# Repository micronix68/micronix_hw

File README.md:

# micronix_hw
Micronix Motorola 68000 Microcomputer hardware development repository

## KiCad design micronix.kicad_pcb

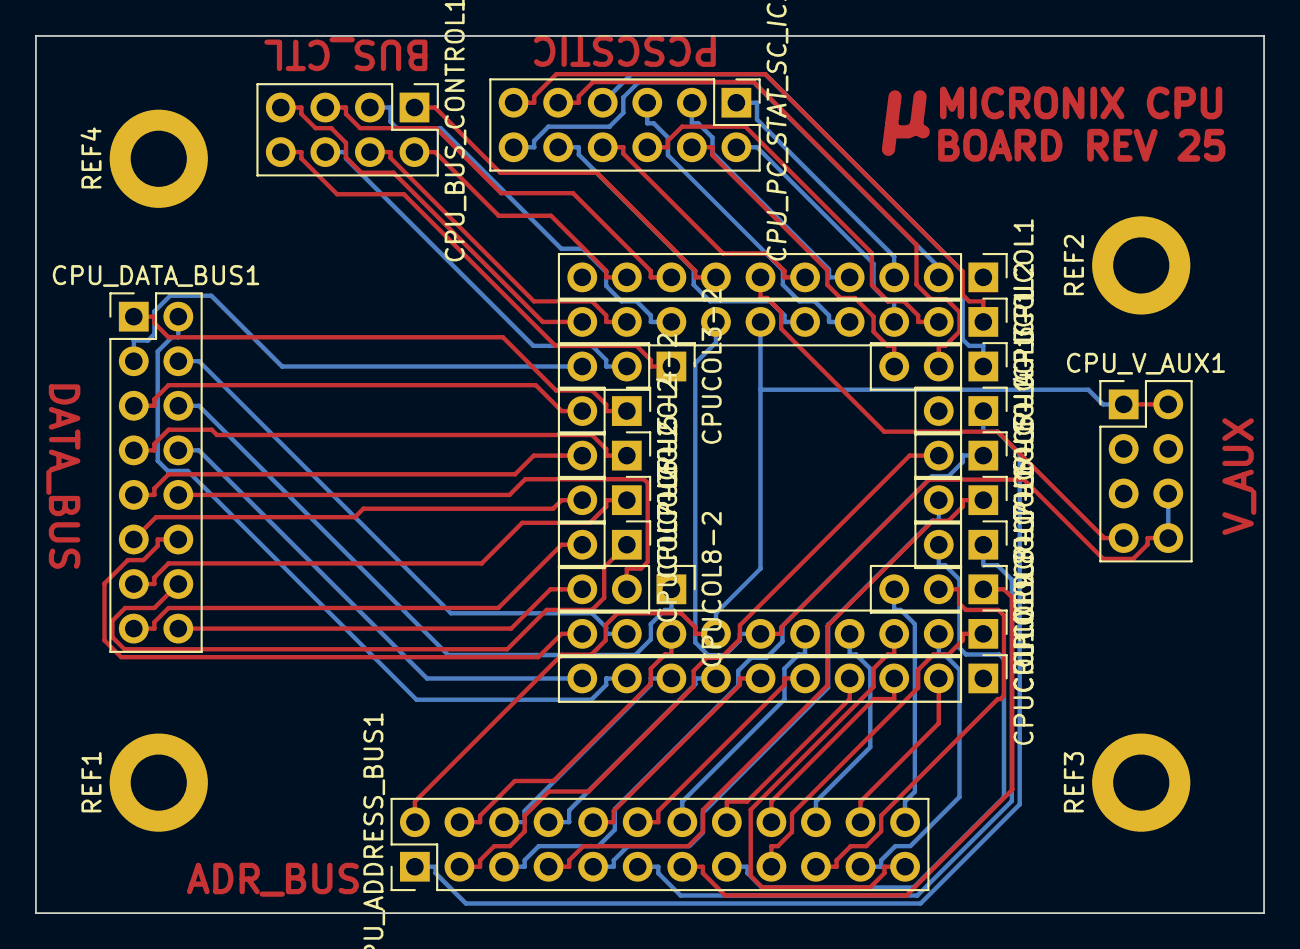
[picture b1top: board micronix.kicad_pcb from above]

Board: 2 copper layers, 70.0 x 50.0 mm, 25 parts (0 on the bottom side), 62 nets.

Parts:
CPUCOL1, CPUCOL2, CPUCOL9, CPUCOL10: Conn_01x10_Female; PinHeader_1x10_P2.54mm_Vertical
CPUCOL3-1, CPUCOL3-2, CPUCOL8-1, CPUCOL8-2: Conn_01x03_Female; PinHeader_1x03_P2.54mm_Vertical
CPUCOL4-1, CPUCOL4-2, CPUCOL5-1, CPUCOL5-2, CPUCOL6-1, CPUCOL6-2, CPUCOL7-1, CPUCOL7-2: Conn_01x02_Female; PinHeader_1x02_P2.54mm_Vertical
CPU_ADDRESS_BUS1: Conn_02x12_Odd_Even; PinHeader_2x12_P2.54mm_Vertical
CPU_BUS_CONTROL1: Conn_02x04_Odd_Even; PinHeader_2x04_P2.54mm_Vertical
CPU_DATA_BUS1: Conn_02x08_Odd_Even; PinHeader_2x08_P2.54mm_Vertical
CPU_PC_STAT_SC_IC1: Conn_02x06_Odd_Even; PinHeader_2x06_P2.54mm_Vertical
CPU_V_AUX1: Conn_02x04_Odd_Even; PinHeader_2x04_P2.54mm_Vertical
REF1, REF2, REF3, REF4: MountingHole_3.2mm_M3_DIN965_Pad

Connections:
/A2: CPUCOL2.10, CPU_BUS_CONTROL1.7
/A3: CPUCOL3-2.3, CPU_DATA_BUS1.3
/A4: CPUCOL4-2.2, CPU_DATA_BUS1.5
/A5: CPUCOL5-2.2, CPU_DATA_BUS1.9
/A6: CPUCOL6-2.2, CPU_DATA_BUS1.11
/A7: CPUCOL7-2.2, CPU_DATA_BUS1.15
/A8: CPUCOL8-2.3, CPU_DATA_BUS1.16
/A9: CPUCOL9.10, CPU_DATA_BUS1.12
/A10: CPUCOL10.10, CPU_DATA_BUS1.8
/B1: CPUCOL1.9, CPU_BUS_CONTROL1.2
/B2: CPUCOL2.9, CPU_BUS_CONTROL1.4
/B3: CPUCOL3-2.2, CPU_BUS_CONTROL1.6
/B4: CPUCOL4-2.1, CPU_DATA_BUS1.1
/B5: CPUCOL5-2.1, CPU_DATA_BUS1.7
/B6: CPUCOL6-2.1, CPU_DATA_BUS1.13
/B7: CPUCOL7-2.1, CPU_DATA_BUS1.14
/B8: CPUCOL8-2.2, CPU_DATA_BUS1.10
/B9: CPUCOL9.9, CPU_DATA_BUS1.4
/B10: CPUCOL10.9, CPU_DATA_BUS1.2
/C1: CPUCOL1.8, CPU_BUS_CONTROL1.5
/C2: CPUCOL2.8, CPU_BUS_CONTROL1.3
/C3: CPUCOL3-2.1, CPU_BUS_CONTROL1.8
/C8: CPUCOL8-2.1, CPU_DATA_BUS1.6
/C9: CPUCOL9.8, CPU_ADDRESS_BUS1.4
/C10: CPUCOL10.8, CPU_ADDRESS_BUS1.6
/D1: CPUCOL1.7, CPU_BUS_CONTROL1.1
/D2: CPUCOL2.7, CPUCOL9.6, CPU_V_AUX1.6, CPU_V_AUX1.8
/D9: CPUCOL2.6, CPUCOL9.7, CPU_ADDRESS_BUS1.2, CPU_V_AUX1.1, CPU_V_AUX1.2
/D10: CPUCOL10.7, CPU_ADDRESS_BUS1.8
/E1: CPUCOL1.6, CPU_V_AUX1.7
/E10: CPUCOL10.6, CPU_ADDRESS_BUS1.10
/F1: CPUCOL1.5, CPU_PC_STAT_SC_IC1.8
/F2: CPUCOL2.5, CPU_PC_STAT_SC_IC1.10
/F9: CPUCOL9.5, CPU_ADDRESS_BUS1.14
/F10: CPUCOL10.5, CPU_ADDRESS_BUS1.12
/G1: CPUCOL1.4, CPU_PC_STAT_SC_IC1.3
/G2: CPUCOL2.4, CPU_PC_STAT_SC_IC1.5
/G9: CPUCOL9.4, CPU_ADDRESS_BUS1.20
/G10: CPUCOL10.4, CPU_ADDRESS_BUS1.16
/H1: CPUCOL1.3, CPU_PC_STAT_SC_IC1.1
/H2: CPUCOL2.3, CPU_PC_STAT_SC_IC1.2
/H3: CPUCOL3-1.3, CPU_PC_STAT_SC_IC1.4
/H8: CPUCOL8-1.3, CPU_ADDRESS_BUS1.24
/H9: CPUCOL9.3, CPU_ADDRESS_BUS1.23
/H10: CPUCOL10.3, CPU_ADDRESS_BUS1.18
/J1: CPUCOL1.2, CPU_PC_STAT_SC_IC1.12
/J2: CPUCOL2.2, CPU_PC_STAT_SC_IC1.6
/J3: CPUCOL3-1.2, CPU_PC_STAT_SC_IC1.9
/J5: CPUCOL5-1.2, CPU_ADDRESS_BUS1.3
/J6: CPUCOL6-1.2, CPU_ADDRESS_BUS1.9
/J7: CPUCOL7-1.2, CPU_ADDRESS_BUS1.15
/J8: CPUCOL8-1.2, CPU_ADDRESS_BUS1.19
/J9: CPUCOL9.2, CPU_ADDRESS_BUS1.21
/J10: CPUCOL10.2, CPU_ADDRESS_BUS1.22
/K2: CPUCOL2.1, CPU_PC_STAT_SC_IC1.11
/K3: CPUCOL3-1.1, CPU_PC_STAT_SC_IC1.7
/K4: CPUCOL4-1.1, CPU_ADDRESS_BUS1.1
/K5: CPUCOL5-1.1, CPU_ADDRESS_BUS1.5
/K6: CPUCOL6-1.1, CPU_ADDRESS_BUS1.7
/K7: CPUCOL7-1.1, CPU_ADDRESS_BUS1.11
/K8: CPUCOL8-1.1, CPU_ADDRESS_BUS1.13
/K9: CPUCOL9.1, CPU_ADDRESS_BUS1.17

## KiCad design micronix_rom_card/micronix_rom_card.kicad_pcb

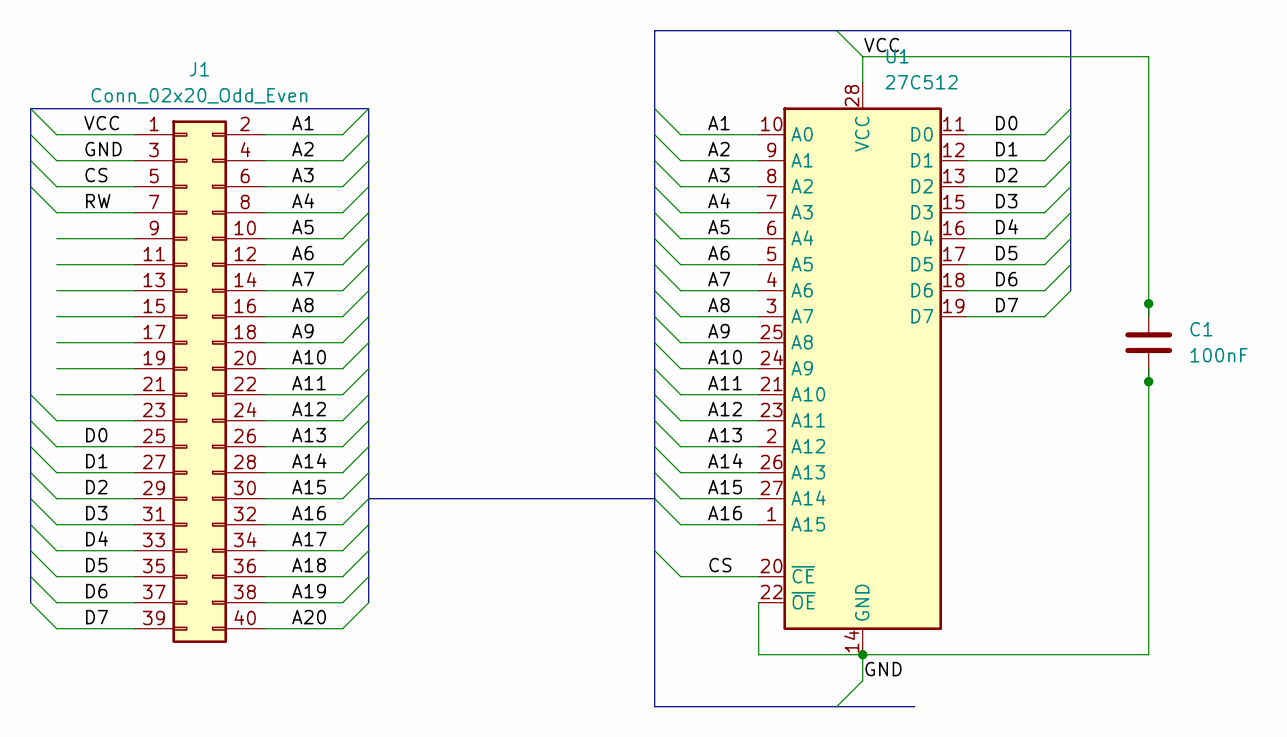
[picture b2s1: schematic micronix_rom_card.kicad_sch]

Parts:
C1: 100nF; CP_Radial_Tantal_D5.0mm_P2.50mm
J1: Conn_02x20_Odd_Even; PinSocket_2x20_P2.54mm_Vertical
U1: 27C512; DIP-28_W15.24mm

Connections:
/A1: J1.2, U1.10 (A0)
/A2: J1.4, U1.9 (A1)
/A3: J1.6, U1.8 (A2)
/A4: J1.8, U1.7 (A3)
/A5: J1.10, U1.6 (A4)
/A6: J1.12, U1.5 (A5)
/A7: J1.14, U1.4 (A6)
/A8: J1.16, U1.3 (A7)
/A9: J1.18, U1.25 (A8)
/A10: J1.20, U1.24 (A9)
/A11: J1.22, U1.21 (A10)
/A12: J1.24, U1.23 (A11)
/A13: J1.26, U1.2 (A12)
/A14: J1.28, U1.26 (A13)
/A15: J1.30, U1.27 (A14)
/A16: J1.32, U1.1 (A15)
/A17: J1.34
/A18: J1.36
/A19: J1.38
/A20: J1.40
/CS: J1.5, U1.20 (~CE)
/D0: J1.25, U1.11 (D0)
/D1: J1.27, U1.12 (D1)
/D2: J1.29, U1.13 (D2)
/D3: J1.31, U1.15 (D3)
/D4: J1.33, U1.16 (D4)
/D5: J1.35, U1.17 (D5)
/D6: J1.37, U1.18 (D6)
/D7: J1.39, U1.19 (D7)
/GND: C1.2, J1.3, U1.14 (GND), U1.22 (~OE)
/RW: J1.7
/VCC: C1.1, J1.1, U1.28 (VCC)

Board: 2 copper layers, 3 parts (0 on the bottom side), 27 nets, no tracks yet.

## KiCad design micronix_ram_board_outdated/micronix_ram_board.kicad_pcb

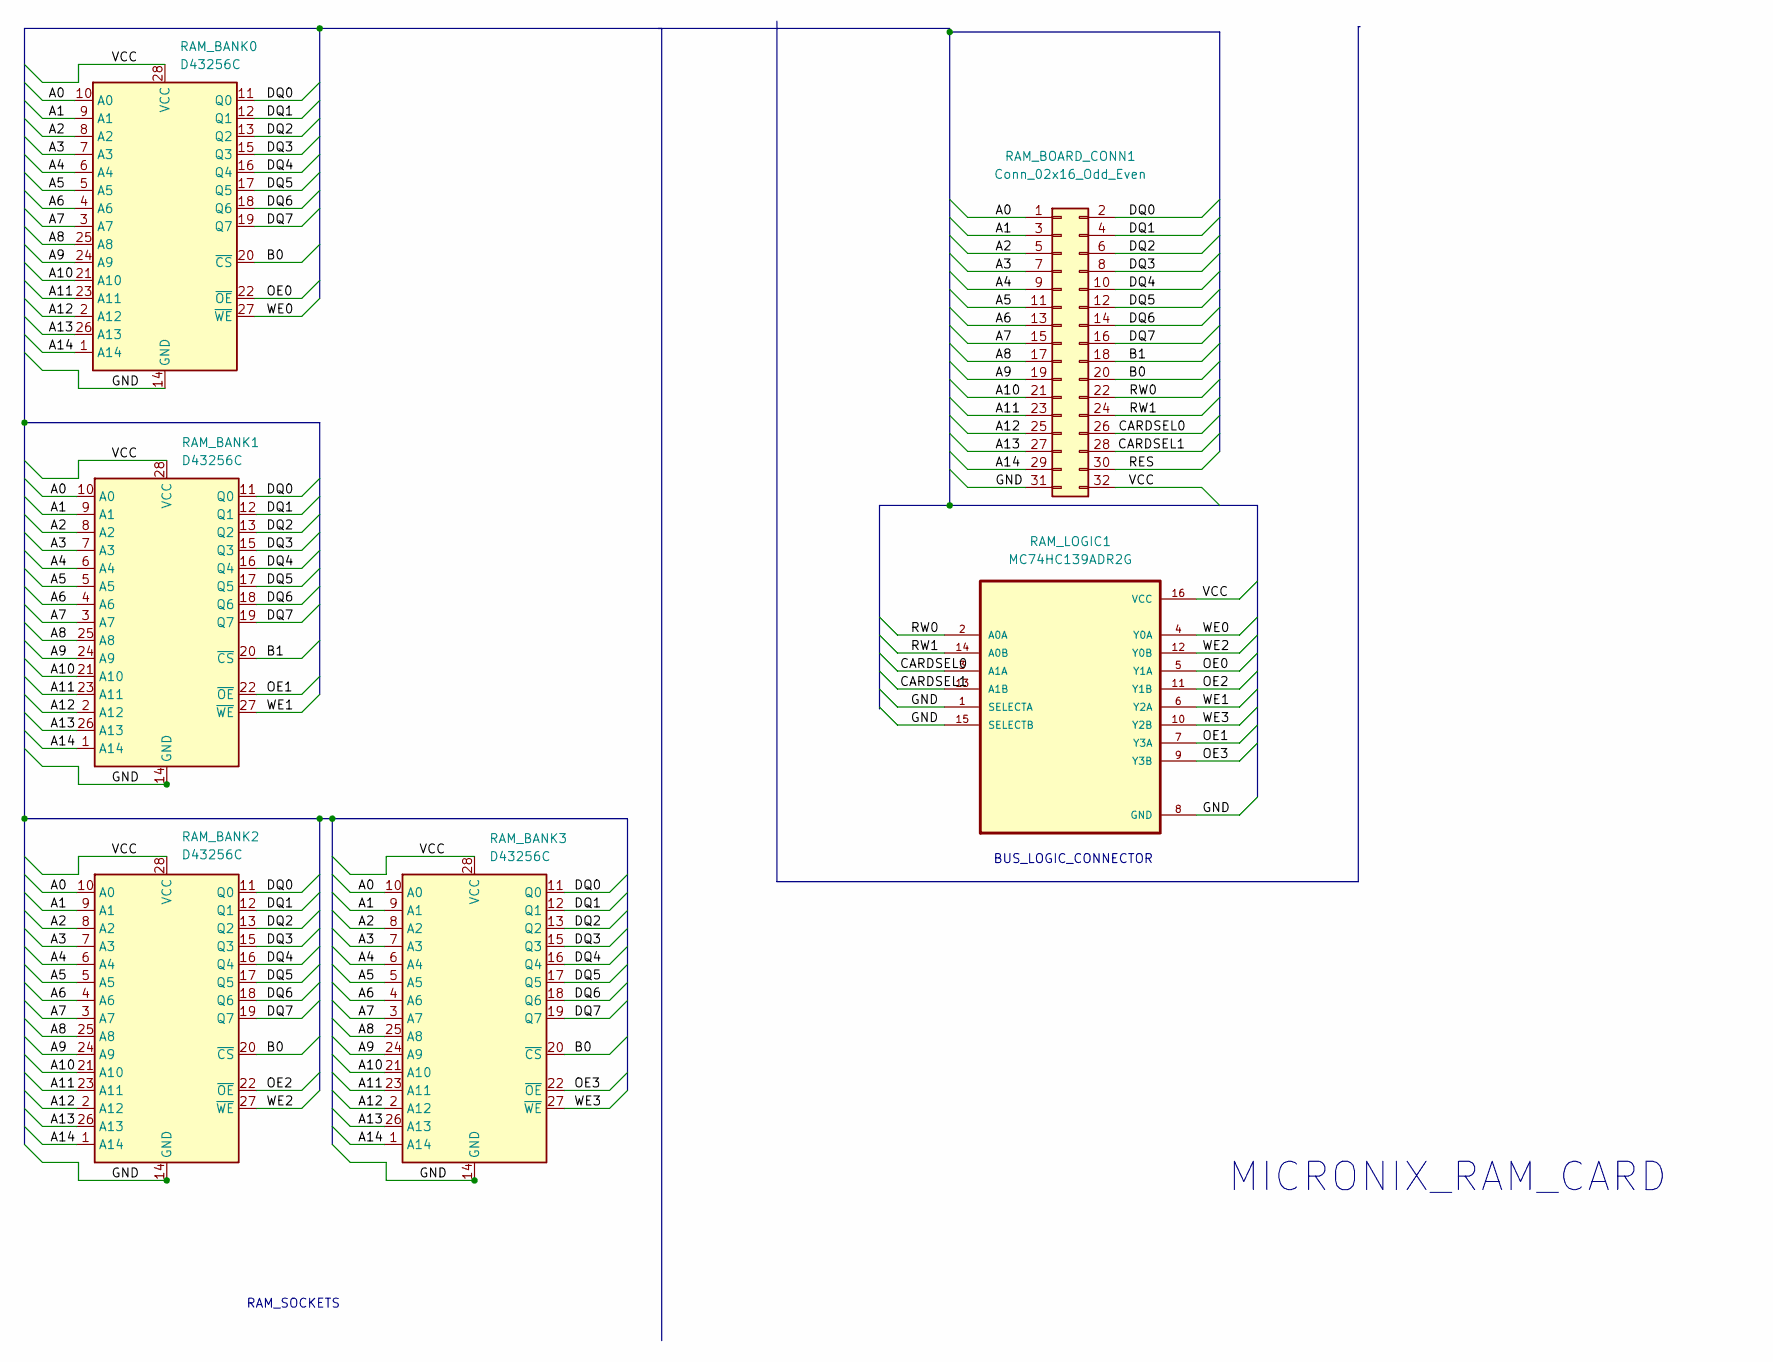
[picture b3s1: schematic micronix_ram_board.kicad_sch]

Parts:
RAM_BANK0, RAM_BANK1, RAM_BANK2, RAM_BANK3: D43256C; DIP-28_W15.24mm
RAM_BOARD_CONN1: Conn_02x16_Odd_Even; PinHeader_2x16_P2.54mm_Vertical
RAM_LOGIC1: MC74HC139ADR2G; SOIC127P600X175-16N

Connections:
/A0: RAM_BANK0.10 (A0), RAM_BANK1.10 (A0), RAM_BANK2.10 (A0), RAM_BANK3.10 (A0), RAM_BOARD_CONN1.1
/A1: RAM_BANK0.9 (A1), RAM_BANK1.9 (A1), RAM_BANK2.9 (A1), RAM_BANK3.9 (A1), RAM_BOARD_CONN1.3
/A2: RAM_BANK0.8 (A2), RAM_BANK1.8 (A2), RAM_BANK2.8 (A2), RAM_BANK3.8 (A2), RAM_BOARD_CONN1.5
/A3: RAM_BANK0.7 (A3), RAM_BANK1.7 (A3), RAM_BANK2.7 (A3), RAM_BANK3.7 (A3), RAM_BOARD_CONN1.7
/A4: RAM_BANK0.6 (A4), RAM_BANK1.6 (A4), RAM_BANK2.6 (A4), RAM_BANK3.6 (A4), RAM_BOARD_CONN1.9
/A5: RAM_BANK0.5 (A5), RAM_BANK1.5 (A5), RAM_BANK2.5 (A5), RAM_BANK3.5 (A5), RAM_BOARD_CONN1.11
/A6: RAM_BANK0.4 (A6), RAM_BANK1.4 (A6), RAM_BANK2.4 (A6), RAM_BANK3.4 (A6), RAM_BOARD_CONN1.13
/A7: RAM_BANK0.3 (A7), RAM_BANK1.3 (A7), RAM_BANK2.3 (A7), RAM_BANK3.3 (A7), RAM_BOARD_CONN1.15
/A8: RAM_BANK0.25 (A8), RAM_BANK1.25 (A8), RAM_BANK2.25 (A8), RAM_BANK3.25 (A8), RAM_BOARD_CONN1.17
/A9: RAM_BANK0.24 (A9), RAM_BANK1.24 (A9), RAM_BANK2.24 (A9), RAM_BANK3.24 (A9), RAM_BOARD_CONN1.19
/A10: RAM_BANK0.21 (A10), RAM_BANK1.21 (A10), RAM_BANK2.21 (A10), RAM_BANK3.21 (A10), RAM_BOARD_CONN1.21
/A11: RAM_BANK0.23 (A11), RAM_BANK1.23 (A11), RAM_BANK2.23 (A11), RAM_BANK3.23 (A11), RAM_BOARD_CONN1.23
/A12: RAM_BANK0.2 (A12), RAM_BANK1.2 (A12), RAM_BANK2.2 (A12), RAM_BANK3.2 (A12), RAM_BOARD_CONN1.25
/A13: RAM_BANK0.26 (A13), RAM_BANK1.26 (A13), RAM_BANK2.26 (A13), RAM_BANK3.26 (A13), RAM_BOARD_CONN1.27
/A14: RAM_BANK0.1 (A14), RAM_BANK1.1 (A14), RAM_BANK2.1 (A14), RAM_BANK3.1 (A14), RAM_BOARD_CONN1.29
/B0: RAM_BANK0.20 (~CS), RAM_BANK2.20 (~CS), RAM_BANK3.20 (~CS), RAM_BOARD_CONN1.20
/B1: RAM_BANK1.20 (~CS), RAM_BOARD_CONN1.18
/CARDSEL0: RAM_BOARD_CONN1.26, RAM_LOGIC1.3 (A1A)
/CARDSEL1: RAM_BOARD_CONN1.28, RAM_LOGIC1.13 (A1B)
/DQ0: RAM_BANK0.11 (Q0), RAM_BANK1.11 (Q0), RAM_BANK2.11 (Q0), RAM_BANK3.11 (Q0), RAM_BOARD_CONN1.2
/DQ1: RAM_BANK0.12 (Q1), RAM_BANK1.12 (Q1), RAM_BANK2.12 (Q1), RAM_BANK3.12 (Q1), RAM_BOARD_CONN1.4
/DQ2: RAM_BANK0.13 (Q2), RAM_BANK1.13 (Q2), RAM_BANK2.13 (Q2), RAM_BANK3.13 (Q2), RAM_BOARD_CONN1.6
/DQ3: RAM_BANK0.15 (Q3), RAM_BANK1.15 (Q3), RAM_BANK2.15 (Q3), RAM_BANK3.15 (Q3), RAM_BOARD_CONN1.8
/DQ4: RAM_BANK0.16 (Q4), RAM_BANK1.16 (Q4), RAM_BANK2.16 (Q4), RAM_BANK3.16 (Q4), RAM_BOARD_CONN1.10
/DQ5: RAM_BANK0.17 (Q5), RAM_BANK1.17 (Q5), RAM_BANK2.17 (Q5), RAM_BANK3.17 (Q5), RAM_BOARD_CONN1.12
/DQ6: RAM_BANK0.18 (Q6), RAM_BANK1.18 (Q6), RAM_BANK2.18 (Q6), RAM_BANK3.18 (Q6), RAM_BOARD_CONN1.14
/DQ7: RAM_BANK0.19 (Q7), RAM_BANK1.19 (Q7), RAM_BANK2.19 (Q7), RAM_BANK3.19 (Q7), RAM_BOARD_CONN1.16
/GND: RAM_BANK0.14 (GND), RAM_BANK1.14 (GND), RAM_BANK2.14 (GND), RAM_BANK3.14 (GND), RAM_BOARD_CONN1.31, RAM_LOGIC1.1 (SELECTA), RAM_LOGIC1.8 (GND), RAM_LOGIC1.15 (SELECTB)
/OE0: RAM_BANK0.22 (~OE), RAM_LOGIC1.5 (Y1A)
/OE1: RAM_BANK1.22 (~OE), RAM_LOGIC1.7 (Y3A)
/OE2: RAM_BANK2.22 (~OE), RAM_LOGIC1.11 (Y1B)
/OE3: RAM_BANK3.22 (~OE), RAM_LOGIC1.9 (Y3B)
/RES: RAM_BOARD_CONN1.30
/RW0: RAM_BOARD_CONN1.22, RAM_LOGIC1.2 (A0A)
/RW1: RAM_BOARD_CONN1.24, RAM_LOGIC1.14 (A0B)
/VCC: RAM_BANK0.28 (VCC), RAM_BANK1.28 (VCC), RAM_BANK2.28 (VCC), RAM_BANK3.28 (VCC), RAM_BOARD_CONN1.32, RAM_LOGIC1.16 (VCC)
/WE0: RAM_BANK0.27 (~WE), RAM_LOGIC1.4 (Y0A)
/WE1: RAM_BANK1.27 (~WE), RAM_LOGIC1.6 (Y2A)
/WE2: RAM_BANK2.27 (~WE), RAM_LOGIC1.12 (Y0B)
/WE3: RAM_BANK3.27 (~WE), RAM_LOGIC1.10 (Y2B)

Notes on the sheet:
RAM_SOCKETS
MICRONIX_RAM_CARD
BUS_LOGIC_CONNECTOR

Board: 2 copper layers, 6 parts (0 on the bottom side), 39 nets, no tracks yet.

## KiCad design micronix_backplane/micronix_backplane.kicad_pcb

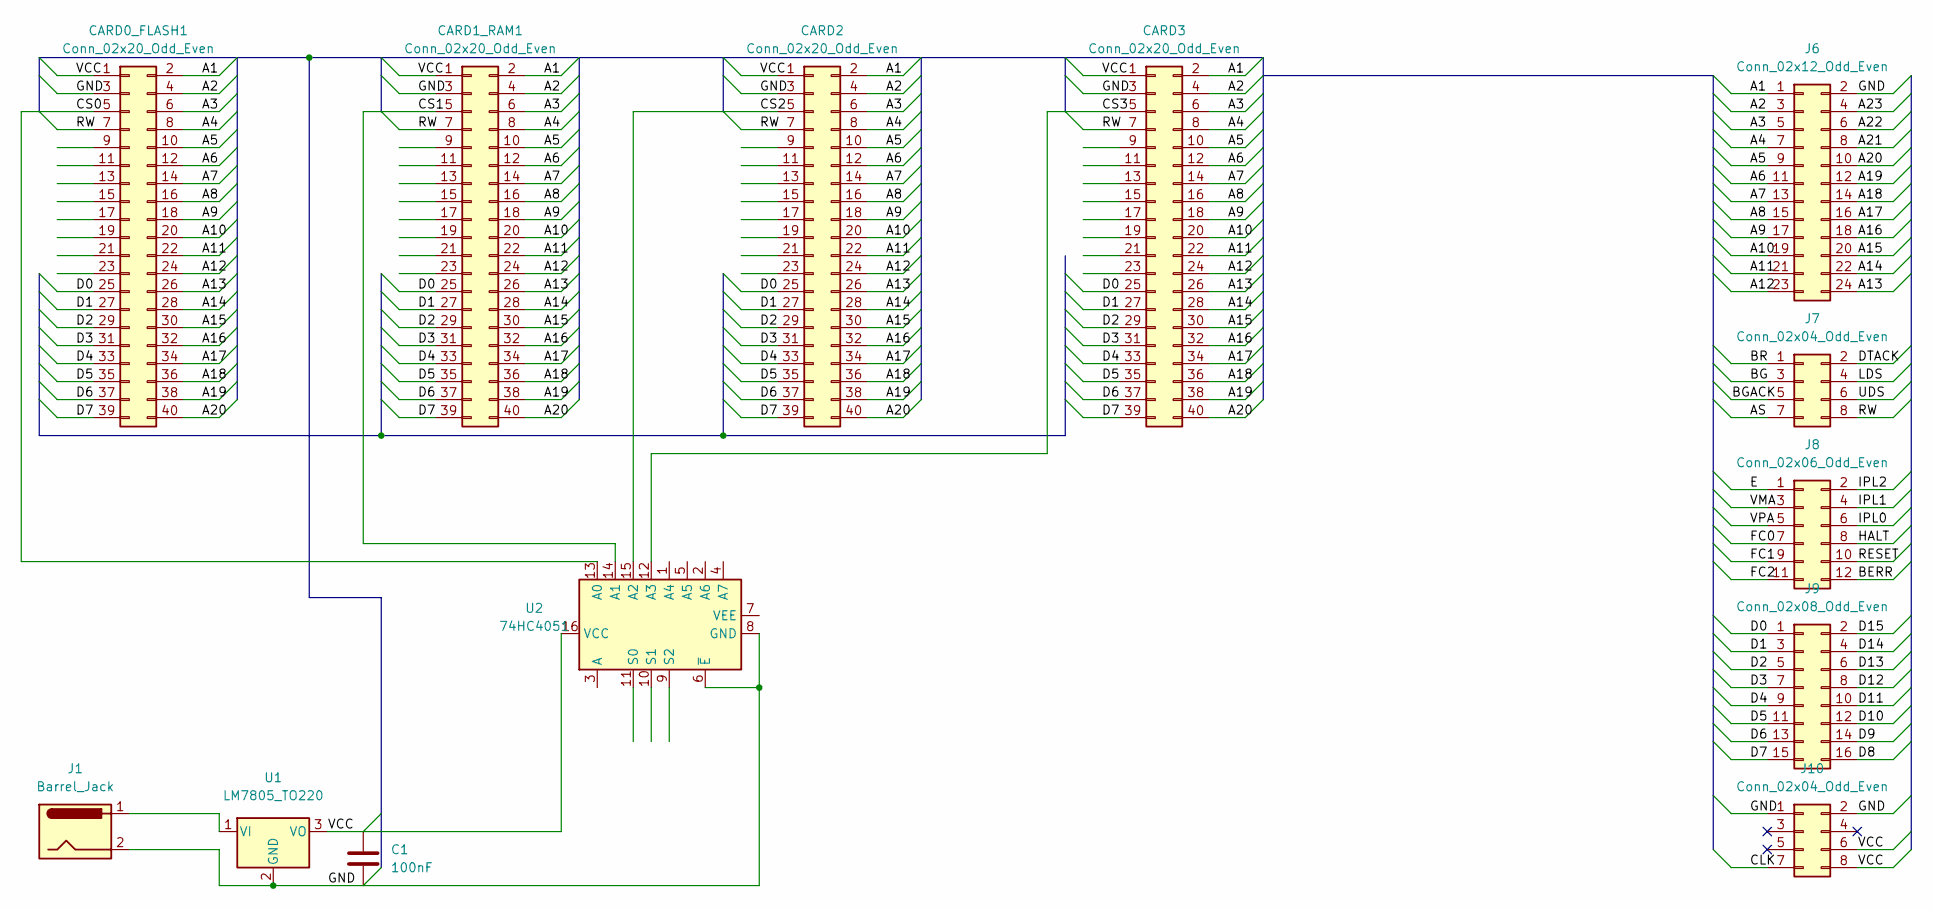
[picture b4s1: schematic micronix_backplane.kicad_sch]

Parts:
C1: 100nF; CP_Radial_Tantal_D5.0mm_P2.50mm
CARD0_FLASH1, CARD1_RAM1, CARD2, CARD3: Conn_02x20_Odd_Even; PinSocket_2x20_P2.54mm_Vertical
J1: Barrel_Jack; BarrelJack_Horizontal
J6: Conn_02x12_Odd_Even; PinSocket_2x12_P2.54mm_Vertical
J7, J10: Conn_02x04_Odd_Even; PinSocket_2x04_P2.54mm_Vertical
J8: Conn_02x06_Odd_Even; PinSocket_2x06_P2.54mm_Vertical
J9: Conn_02x08_Odd_Even; PinSocket_2x08_P2.54mm_Vertical
U1: LM7805_TO220; TO-220-3_Vertical
U2: 74HC4051; SO-16_3.9x9.9mm_P1.27mm

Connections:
/A1: CARD0_FLASH1.2, CARD1_RAM1.2, CARD2.2, CARD3.2, J6.1
/A2: CARD0_FLASH1.4, CARD1_RAM1.4, CARD2.4, CARD3.4, J6.3
/A3: CARD0_FLASH1.6, CARD1_RAM1.6, CARD2.6, CARD3.6, J6.5
/A4: CARD0_FLASH1.8, CARD1_RAM1.8, CARD2.8, CARD3.8, J6.7
/A5: CARD0_FLASH1.10, CARD1_RAM1.10, CARD2.10, CARD3.10, J6.9
/A6: CARD0_FLASH1.12, CARD1_RAM1.12, CARD2.12, CARD3.12, J6.11
/A7: CARD0_FLASH1.14, CARD1_RAM1.14, CARD2.14, CARD3.14, J6.13
/A8: CARD0_FLASH1.16, CARD1_RAM1.16, CARD2.16, CARD3.16, J6.15
/A9: CARD0_FLASH1.18, CARD1_RAM1.18, CARD2.18, CARD3.18, J6.17
/A10: CARD0_FLASH1.20, CARD1_RAM1.20, CARD2.20, CARD3.20, J6.19
/A11: CARD0_FLASH1.22, CARD1_RAM1.22, CARD2.22, CARD3.22, J6.21
/A12: CARD0_FLASH1.24, CARD1_RAM1.24, CARD2.24, CARD3.24, J6.23
/A13: CARD0_FLASH1.26, CARD1_RAM1.26, CARD2.26, CARD3.26, J6.24
/A14: CARD0_FLASH1.28, CARD1_RAM1.28, CARD2.28, CARD3.28, J6.22
/A15: CARD0_FLASH1.30, CARD1_RAM1.30, CARD2.30, CARD3.30, J6.20
/A16: CARD0_FLASH1.32, CARD1_RAM1.32, CARD2.32, CARD3.32, J6.18
/A17: CARD0_FLASH1.34, CARD1_RAM1.34, CARD2.34, CARD3.34, J6.16
/A18: CARD0_FLASH1.36, CARD1_RAM1.36, CARD2.36, CARD3.36, J6.14
/A19: CARD0_FLASH1.38, CARD1_RAM1.38, CARD2.38, CARD3.38, J6.12
/A20: CARD0_FLASH1.40, CARD1_RAM1.40, CARD2.40, CARD3.40, J6.10
/A21: J6.8
/A22: J6.6
/A23: J6.4
/AS: J7.7
/BERR: J8.12
/BG: J7.3
/BGACK: J7.5
/BR: J7.1
/CLK: J10.7
/CS0: CARD0_FLASH1.5, U2.13 (A0)
/CS1: CARD1_RAM1.5, U2.14 (A1)
/CS2: CARD2.5, U2.15 (A2)
/CS3: CARD3.5, U2.12 (A3)
/D0: CARD0_FLASH1.25, CARD1_RAM1.25, CARD2.25, CARD3.25, J9.1
/D1: CARD0_FLASH1.27, CARD1_RAM1.27, CARD2.27, CARD3.27, J9.3
/D2: CARD0_FLASH1.29, CARD1_RAM1.29, CARD2.29, CARD3.29, J9.5
/D3: CARD0_FLASH1.31, CARD1_RAM1.31, CARD2.31, CARD3.31, J9.7
/D4: CARD0_FLASH1.33, CARD1_RAM1.33, CARD2.33, CARD3.33, J9.9
/D5: CARD0_FLASH1.35, CARD1_RAM1.35, CARD2.35, CARD3.35, J9.11
/D6: CARD0_FLASH1.37, CARD1_RAM1.37, CARD2.37, CARD3.37, J9.13
/D7: CARD0_FLASH1.39, CARD1_RAM1.39, CARD2.39, CARD3.39, J9.15
/D8: J9.16
/D9: J9.14
/D10: J9.12
/D11: J9.10
/D12: J9.8
/D13: J9.6
/D14: J9.4
/D15: J9.2
/DTACK: J7.2
/E: J8.1
/FC0: J8.7
/FC1: J8.9
/FC2: J8.11
/GND: C1.2, CARD0_FLASH1.3, CARD1_RAM1.3, CARD2.3, CARD3.3, J1.2, J6.2, J10.1, J10.2, U1.2 (GND), U2.6 (~E), U2.8 (GND)
/HALT: J8.8
/IPL0: J8.6
/IPL1: J8.4
/IPL2: J8.2
/LDS: J7.4
/RESET: J8.10
/RW: CARD0_FLASH1.7, CARD1_RAM1.7, CARD2.7, CARD3.7, J7.8
/UDS: J7.6
/VCC: C1.1, CARD0_FLASH1.1, CARD1_RAM1.1, CARD2.1, CARD3.1, J10.6, J10.8, U1.3 (VO), U2.16 (VCC)
/VMA: J8.3
/VPA: J8.5
unnamed: J1.1, U1.1 (VI)

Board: 2 copper layers, 13 parts (0 on the bottom side), 36 nets, no tracks yet.

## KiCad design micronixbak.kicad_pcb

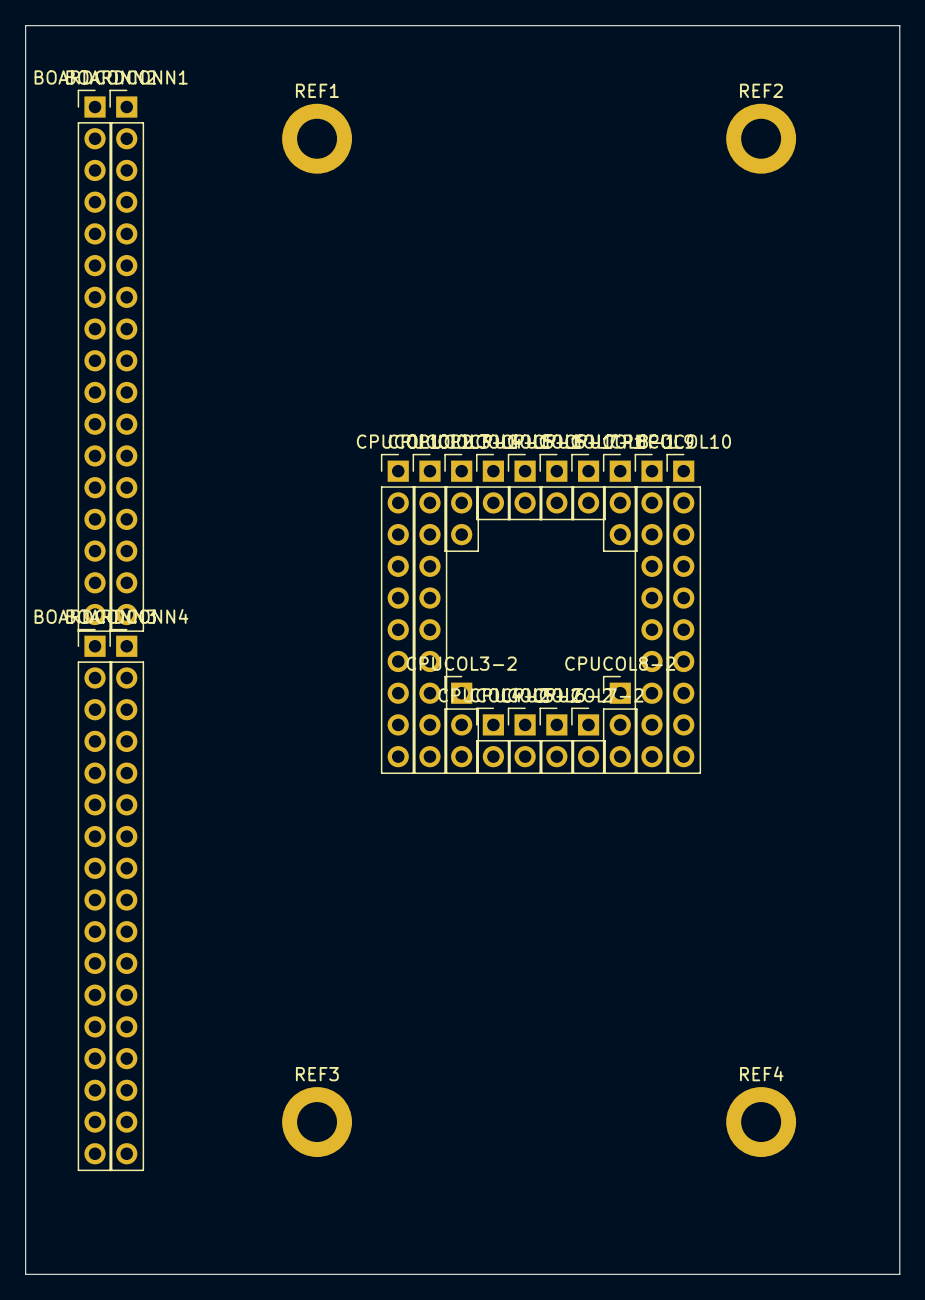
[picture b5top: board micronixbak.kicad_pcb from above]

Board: 2 copper layers, 70.0 x 100.0 mm, 24 parts (0 on the bottom side), 68 nets, no tracks yet.

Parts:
BOARDCONN1, BOARDCONN2, BOARDCONN3, BOARDCONN4: Conn_01x17_Female; PinHeader_1x17_P2.54mm_Vertical
CPUCOL1, CPUCOL2, CPUCOL9, CPUCOL10: Conn_01x10_Female; PinHeader_1x10_P2.54mm_Vertical
CPUCOL3-1, CPUCOL3-2, CPUCOL8-1, CPUCOL8-2: Conn_01x03_Female; PinHeader_1x03_P2.54mm_Vertical
CPUCOL4-1, CPUCOL4-2, CPUCOL5-1, CPUCOL5-2, CPUCOL6-1, CPUCOL6-2, CPUCOL7-1, CPUCOL7-2: Conn_01x02_Female; PinHeader_1x02_P2.54mm_Vertical
REF1, REF2, REF3, REF4: MountingHole_3.2mm_M3_DIN965_Pad

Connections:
/A1: BOARDCONN1.10, CPUCOL1.10
/A2: BOARDCONN2.3, CPUCOL2.10
/A3: BOARDCONN2.9, CPUCOL3-2.3
/A4: BOARDCONN2.13, CPUCOL4-2.2
/A5: BOARDCONN2.17, CPUCOL5-2.2
/A6: BOARDCONN3.4, CPUCOL6-2.2
/A7: BOARDCONN3.8, CPUCOL7-2.2
/A8: BOARDCONN3.14, CPUCOL8-2.3
/A9: BOARDCONN4.7, CPUCOL9.10
/A10: BOARDCONN4.17, CPUCOL10.10
/B1: BOARDCONN1.9, CPUCOL1.9
/B2: BOARDCONN2.2, CPUCOL2.9
/B3: BOARDCONN2.8, CPUCOL3-2.2
/B4: BOARDCONN2.12, CPUCOL4-2.1
/B5: BOARDCONN2.16, CPUCOL5-2.1
/B6: BOARDCONN3.3, CPUCOL6-2.1
/B7: BOARDCONN3.7, CPUCOL7-2.1
/B8: BOARDCONN3.13, CPUCOL8-2.2
/B9: BOARDCONN4.6, CPUCOL9.9
/B10: BOARDCONN4.16, CPUCOL10.9
/C1: BOARDCONN1.8, CPUCOL1.8
/C2: BOARDCONN2.1, CPUCOL2.8
/C3: BOARDCONN2.7, CPUCOL3-2.1
/C8: BOARDCONN3.12, CPUCOL8-2.1
/C9: BOARDCONN4.5, CPUCOL9.8
/C10: BOARDCONN4.15, CPUCOL10.8
/D1: BOARDCONN1.7, CPUCOL1.7
/D2: BOARDCONN1.17, CPUCOL2.7
/D9: BOARDCONN4.4, CPUCOL9.7
/D10: BOARDCONN4.14, CPUCOL10.7
/E1: BOARDCONN1.6, CPUCOL1.6
/E2: BOARDCONN1.16, CPUCOL2.6
/E9: BOARDCONN4.3, CPUCOL9.6
/E10: BOARDCONN4.13, CPUCOL10.6
/F1: BOARDCONN1.5, CPUCOL1.5
/F2: BOARDCONN1.15, CPUCOL2.5
/F9: BOARDCONN4.2, CPUCOL9.5
/F10: BOARDCONN4.12, CPUCOL10.5
/G1: BOARDCONN1.4, CPUCOL1.4
/G2: BOARDCONN1.14, CPUCOL2.4
/G9: BOARDCONN4.1, CPUCOL9.4
/G10: BOARDCONN4.11, CPUCOL10.4
/H1: BOARDCONN1.3, CPUCOL1.3
/H2: BOARDCONN1.13, CPUCOL2.3
/H3: BOARDCONN2.6, CPUCOL3-1.3
/H8: BOARDCONN3.11, CPUCOL8-1.3
/H9: BOARDCONN3.17, CPUCOL9.3
/H10: BOARDCONN4.10, CPUCOL10.3
/J1: BOARDCONN1.2, CPUCOL1.2
/J2: BOARDCONN1.12, CPUCOL2.2
/J3: BOARDCONN2.5, CPUCOL3-1.2
/J4: BOARDCONN2.11, CPUCOL4-1.2
/J5: BOARDCONN2.15, CPUCOL5-1.2
/J6: BOARDCONN3.2, CPUCOL6-1.2
/J7: BOARDCONN3.6, CPUCOL7-1.2
/J8: BOARDCONN3.10, CPUCOL8-1.2
/J9: BOARDCONN3.16, CPUCOL9.2
/J10: BOARDCONN4.9, CPUCOL10.2
/K1: BOARDCONN1.1, CPUCOL1.1
/K2: BOARDCONN1.11, CPUCOL2.1
/K3: BOARDCONN2.4, CPUCOL3-1.1
/K4: BOARDCONN2.10, CPUCOL4-1.1
/K5: BOARDCONN2.14, CPUCOL5-1.1
/K6: BOARDCONN3.1, CPUCOL6-1.1
/K7: BOARDCONN3.5, CPUCOL7-1.1
/K8: BOARDCONN3.9, CPUCOL8-1.1
/K9: BOARDCONN3.15, CPUCOL9.1
/K10: BOARDCONN4.8, CPUCOL10.1

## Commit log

2022-07-18 added files from local proj
